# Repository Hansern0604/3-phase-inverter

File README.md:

# Basic Git Commands

Dette er en enkel oversikt over de grunnleggende Git-kommandoene du trenger for å jobbe effektivt i et GitHub-samarbeidsprosjekt.

## 1. **Konfigurering av Git**

# Sett opp ditt navn og e-post (kun første gang)
git config --global user.name "Ditt Navn"
git config --global user.email "din.email@example.com"

## 2. **Klon et eksisterende repository**

git clone <repository-URL>

## 3. **Naviger inn i repository-mappen**

cd <repository-folder>

## 4. **Opprette og bytte branch**

# Opprett en ny branch
git checkout -b ny-feature

# Bytt til en eksisterende branch
git checkout main

Eller (hvis du bruker nyere Git-versjoner):

git switch -c ny-feature

## 5. **Hente de nyeste oppdateringene fra GitHub**

# Oppdater din lokale main-branch
git checkout main
git pull origin main

## 6. **Legge til endringer og commit'e**

# Se hvilke filer som er endret
git status

# Legg til alle filer for commit
git add .

# Lag en commit med en beskrivelse
git commit -m "Beskrivelse av endringen"

## 7. **Pushe endringer til GitHub**

# Push din branch til GitHub
git push origin ny-feature

## 8. **Hente endringer fra en annen contributor**

git pull origin main

## 9. **Løse merge-konflikter**

- Åpne filene som har konflikter (markert med `<<<<<<<`, `=======`, `>>>>>>>`)
- Rediger manuelt og behold den riktige versjonen
- Når løst, kjør:

git add .
git commit -m "Løst merge-konflikt"
git push origin main

## 10. **Opprette en Pull Request (PR)**

1. Push din branch til GitHub
2. Gå til repositoryet på GitHub
3. Klikk "Compare & pull request"
4. Skriv en kort beskrivelse og opprett PR

## 11. **Slette en branch etter merging**

# Slett en lokal branch
git branch -d ny-feature

# Slett en remote branch
git push origin --delete ny-feature

## 12. **Bruke stash for å lagre midlertidige endringer**

git stash        # Lagre endringene midlertidig
git stash pop    # Hente tilbake endringene

Dette er de mest brukte Git-kommandoene for et samarbeidsprosjekt. 🚀

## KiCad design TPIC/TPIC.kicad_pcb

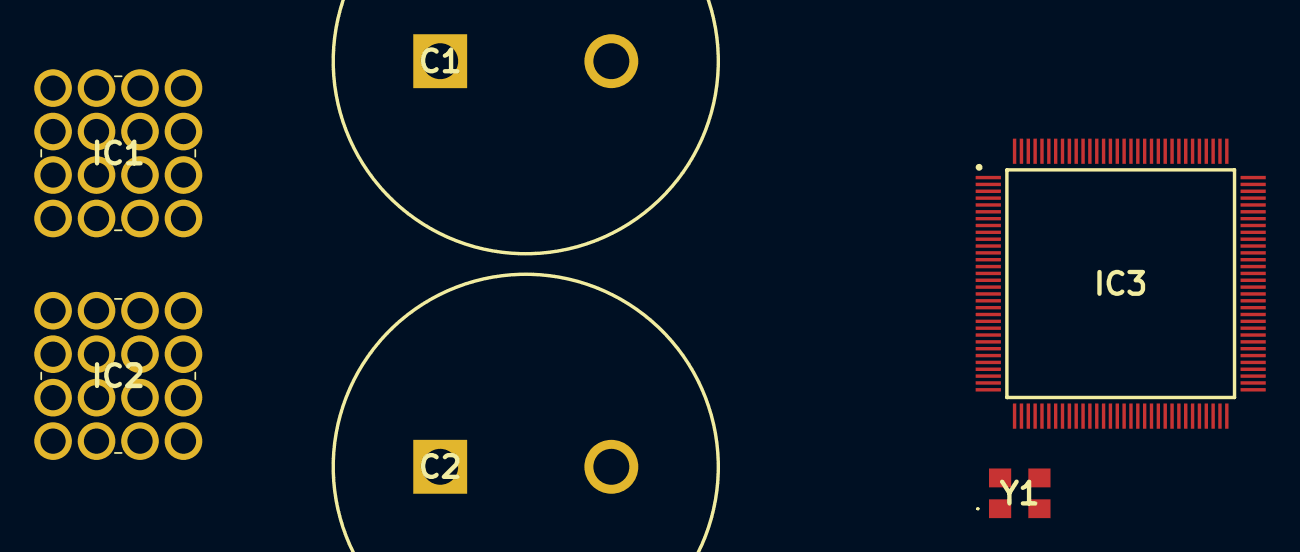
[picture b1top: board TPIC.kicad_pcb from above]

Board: 2 copper layers, 6 parts (0 on the bottom side), 2 nets, no tracks yet.

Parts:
C1, C2: MAL225952471E3; CAPPRD1000W190D2250H3700
IC1, IC2: 7461383
IC3: STM32G474QET6; QFP40P1600X1600X160-128N
Y1: ECS-80-10-33-CGN-TR3; ECS801033CGNTR3

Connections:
/Connectors/Vin+: C1.1 (+), C2.1 (+), IC1.1, IC1.2, IC1.3, IC1.4, IC1.5, IC1.6, IC1.7, IC1.8, IC1.9, IC1.10, IC1.11, IC1.12, IC1.13, IC1.14, IC1.15, IC1.16
/Connectors/Vin-: C1.2 (-), C2.2 (-), IC2.1, IC2.2, IC2.3, IC2.4, IC2.5, IC2.6, IC2.7, IC2.8, IC2.9, IC2.10, IC2.11, IC2.12, IC2.13, IC2.14, IC2.15, IC2.16

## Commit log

2025-02-21 added python file
2025-02-21 La til Library fil
2025-02-21 testertester
2025-02-21 Testing
2025-02-21 lagt til en readme fil
2025-02-21 Oppdatering av filer
2025-02-21 Opdpatering av filer
2025-02-21 Oppdatering
2025-02-23 First schematic changes
2025-02-25 added some files
2025-02-25 did some work to the schematic reagrding the MCU
